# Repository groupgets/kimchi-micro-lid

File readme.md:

# kimχ micro lid KiCad project template

This template lets you create lid expansion boards for the [kimχ micro i.MX8M Mini SBC](https://labs.groupgets.com/kimchi-micro).

This project should include everything you need to make an expansion board, including an eeprom
that can be used to identify your lid and automatically load the correct configuration files (with
some software work to support this).

## How to use this project

This project is to be used with KiCad's "New Project from Template" function.

### Download with GitHub

On GitHub you can select Clone or Download -> Download Zip. Then expand the archive and move it into your user's KiCad templates directory: `$HOME/kicad/template/`. You may have to create this directory if it doesn't exist.

In KiCad, select File > New Project > New Project From Template, and select User Templates. You can then select the kimχ micro - LID project in this list.

### Clone with GitHub

Alternatively, you can create a new GitHub project from this template by selecting Use This Template, above. From there you clone the new project locally and open it directly with KiCad.

Important Note
============
GroupGets does not provide coding, firmware, or software support of any kind and will not respond to related requests. All software and firmware provided by GroupGets are offered solely as examples or potential starting points. These repositories may be outdated and are not guaranteed to function as intended.

We do not accept returns or offer replacements due to issues related to software, firmware, or code compatibility.

The software is provided "AS IS", without warranty of any kind, express or implied, including but not limited to the warranties of merchantability, fitness for a particular purpose and non-infringement. In no event shall the authors or copyright holders be liable for any claim, damages, or other liability, whether in an action of contract, tort, or otherwise, arising from, out of, or in connection with the software or the use or other dealings in the software.

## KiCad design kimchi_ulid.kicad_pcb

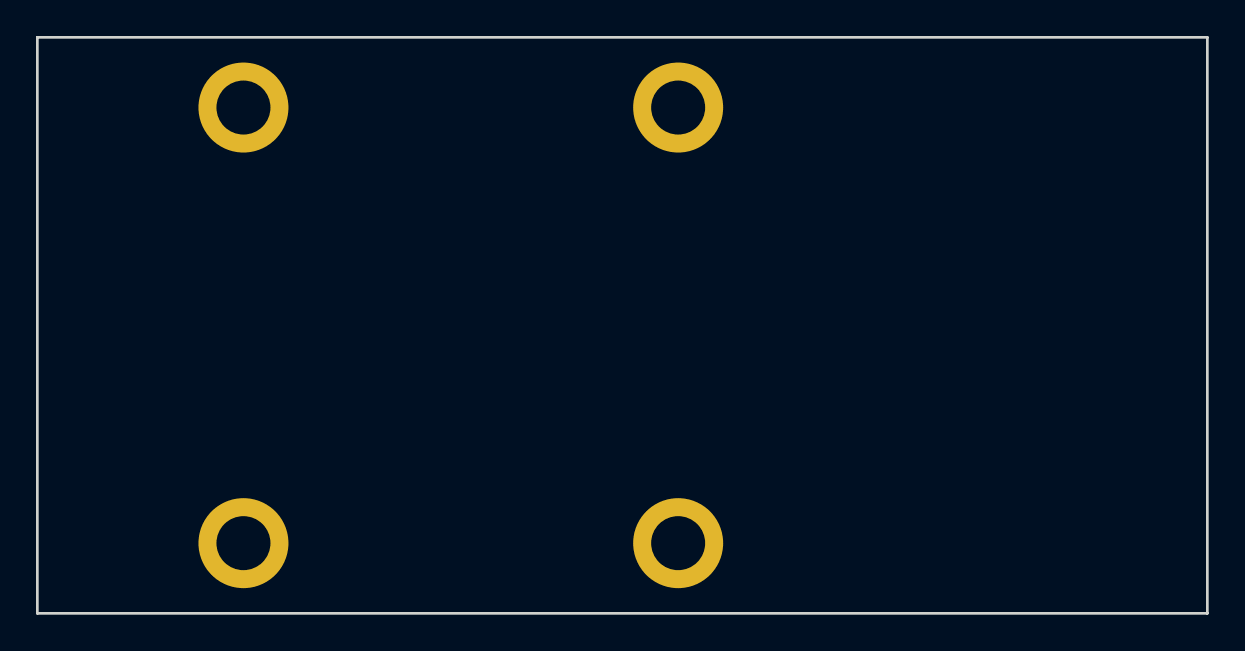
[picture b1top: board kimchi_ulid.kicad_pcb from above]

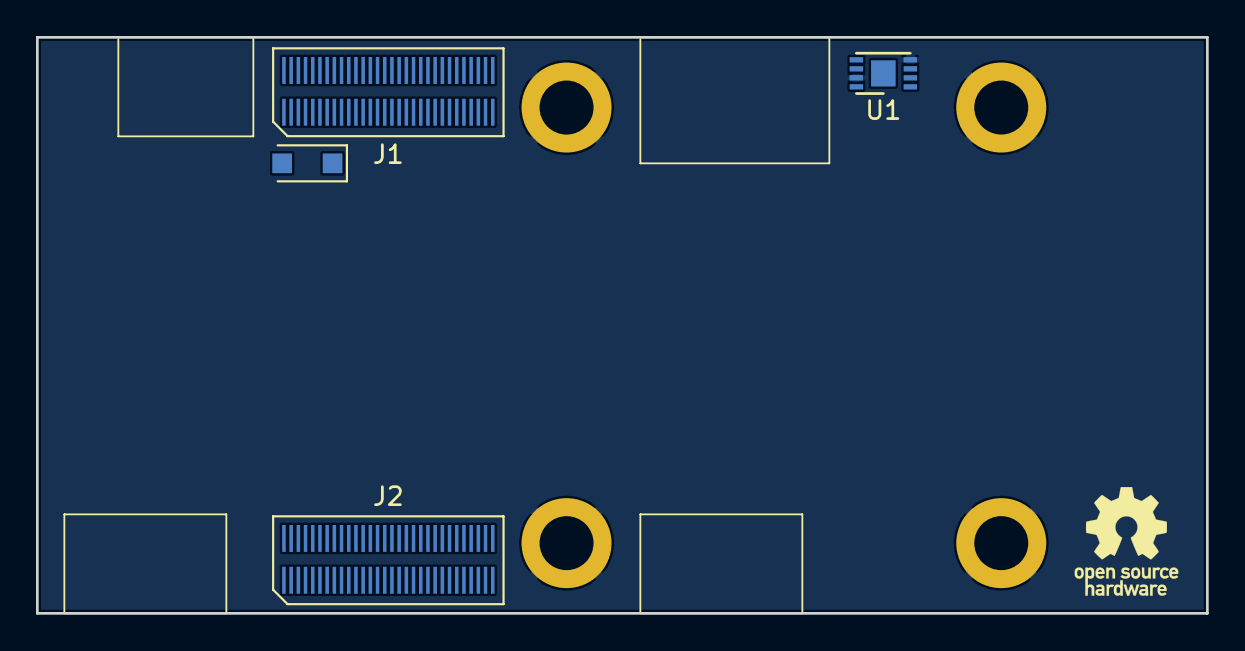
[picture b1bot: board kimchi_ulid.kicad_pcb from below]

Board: 4 copper layers, 65.0 x 32.0 mm, 10 parts (10 on the bottom side), 7 nets, no tracks yet.

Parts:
D1: PMEG1020EH; D_SOD-123F
H1, H2, H3, H4: MountingHole_Pad; MountingHole_M2_Standoff
J1, J2: DF40HC(3.5)-60DS
K1: KIMCHI_MICRO
LOGO1: Logo_Open_Hardware_Small; OSHW-Logo_5.7x6mm_SilkScreen
U1: 24C32; DFN-8-1EP_3x2mm_P0.5mm_EP1.36x1.46mm

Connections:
GND: H1.1, H2.1, H3.1, H4.1, J1.12, J1.13, J1.14, J2.38, J2.39, J2.40, J2.41, J2.50, J2.51, J2.52, J2.53, U1.4, U1.7
I2C4_SCL: J1.16, U1.6
I2C4_SDA: J1.15, U1.5
VCHG: D1.1, J1.52, J1.53, J1.54, J1.55, J1.56
VDD_1V8: J2.43, J2.44, J2.45
VDD_3V3: J2.55, J2.56, J2.57, U1.1, U1.2, U1.3, U1.8
VDD_5V: J1.7, J1.8, J1.9, J1.10

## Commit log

2020-03-03 Create KiCad template for kimchi micro lid
2020-04-09 Remove user comments left over from project creation
2020-04-09 Added kicad meta information for project template
2020-04-09 add project readme
2021-06-22 Updates for 0.92 version
2021-06-24 Set solder mask clearances to zero
2025-10-03 Adding meta data required for KiCad 9 templates.
2025-10-03 Update template to be compatible with kicad 9
